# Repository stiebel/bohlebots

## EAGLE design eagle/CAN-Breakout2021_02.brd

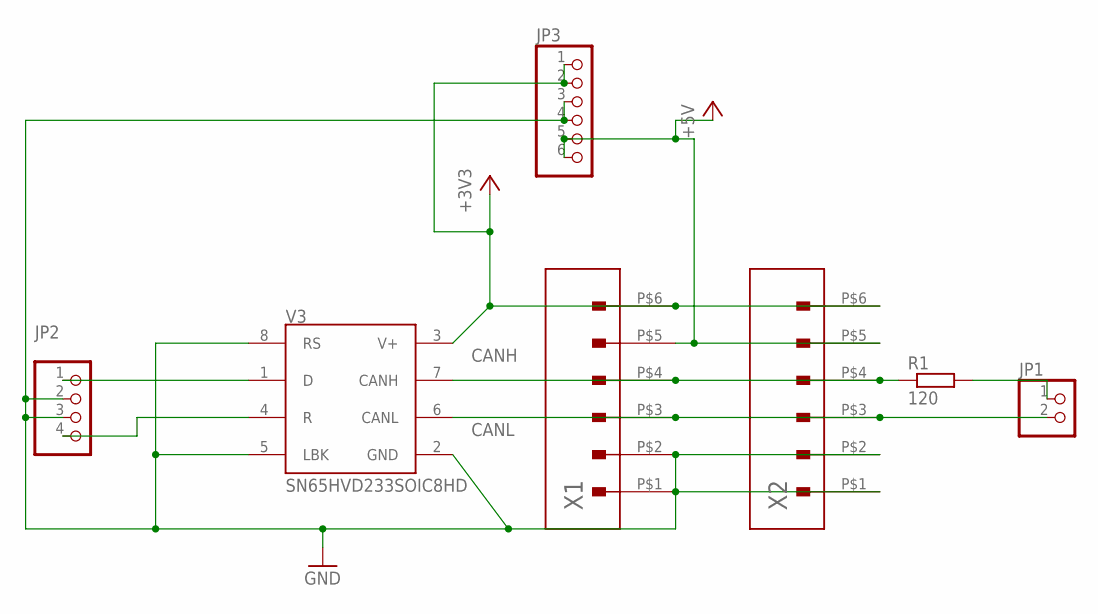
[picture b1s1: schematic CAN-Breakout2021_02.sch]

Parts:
JP1: PINHD-1X2/90; 1X02/90
JP2: PINHD-1X4; 1X04
JP3: PINHD-1X6; 1X06
R1: 120; R0603
V3: SN65HVD233SOIC8HD; SO08
X1, X2: MOLEX104078-0610

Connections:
+3V3: JP3.1, JP3.2, V3.3 (V+), X1.P$6 (6), X2.P$6 (6)
+5V: JP3.5, JP3.6, X1.P$5 (5), X2.P$5 (5)
CANH: R1.1, V3.7 (CANH), X1.P$4 (4), X2.P$4 (4)
CANL: JP1.2, V3.6 (CANL), X1.P$3 (3), X2.P$3 (3)
GND: JP2.2, JP2.3, JP3.3, JP3.4, V3.2 (GND), V3.5 (LBK), V3.8 (RS), X1.P$1 (1), X1.P$2 (2), X2.P$1 (1), X2.P$2 (2)
unnamed: JP1.1, R1.2
unnamed: JP2.1, V3.1 (D)
unnamed: JP2.4, V3.4 (R)

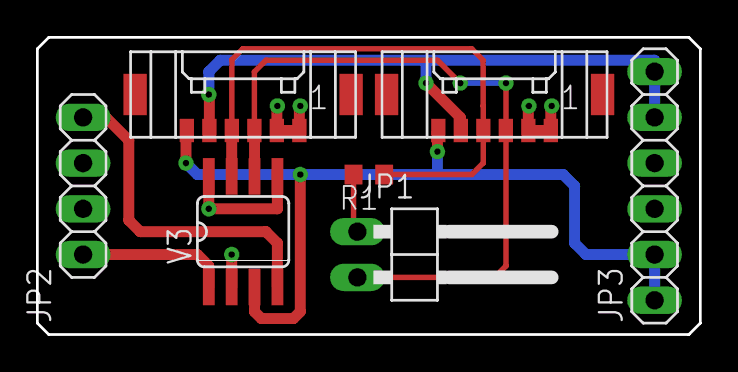
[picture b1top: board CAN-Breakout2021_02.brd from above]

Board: 2 copper layers, 36.8 x 16.5 mm, 7 parts (0 on the bottom side), 8 nets.

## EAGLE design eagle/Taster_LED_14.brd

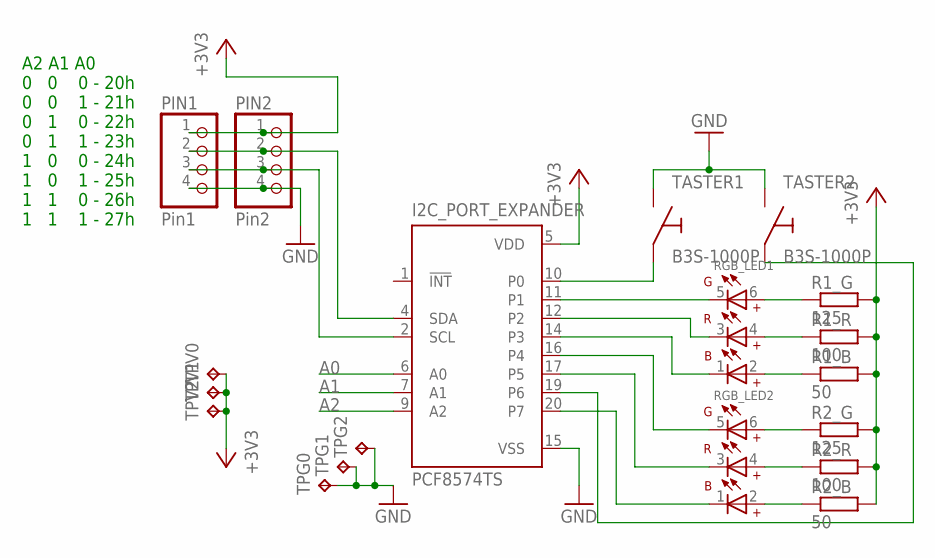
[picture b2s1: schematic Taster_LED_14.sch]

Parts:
I2C_PORT_EXPANDER: PCF8574TS; SSOP20
PIN1: Pin1; 1X04
PIN2: Pin2; 1X04
R1_B, R2_B: 50; R0603
R1_G, R2_G: 125; R0603
R1_R, R2_R: 100; R0603
RGB_LED1, RGB_LED2: WL-SFTW_3528_PLCC6_150352M173300; WL-SFTW_3528_PLCC6
TASTER1, TASTER2: B3S-1000P; B3S-100P
TPG0, TPG1, TPG2: TPTP06SQ; TP06SQ
TPV0, TPV1, TPV2: TPTP06SQ; TP06SQ

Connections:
+3V3: I2C_PORT_EXPANDER.5 (VDD), PIN1.1, PIN2.1, R1_B.2, R1_G.2, R1_R.2, R2_B.2, R2_G.2, R2_R.2, TPV0.TP, TPV1.TP, TPV2.TP
A0: I2C_PORT_EXPANDER.6 (A0)
A1: I2C_PORT_EXPANDER.7 (A1)
A2: I2C_PORT_EXPANDER.9 (A2)
CLK: I2C_PORT_EXPANDER.2 (SCL), PIN1.3, PIN2.3
DATA: I2C_PORT_EXPANDER.4 (SDA), PIN1.2, PIN2.2
GND: I2C_PORT_EXPANDER.15 (VSS), PIN1.4, PIN2.4, TASTER1.3 (2), TASTER2.3 (2), TPG0.TP, TPG1.TP, TPG2.TP
unnamed: I2C_PORT_EXPANDER.11 (P1), RGB_LED1.5
unnamed: R2_B.1, RGB_LED2.2
unnamed: R2_R.1, RGB_LED2.4
unnamed: R2_G.1, RGB_LED2.6
unnamed: R1_G.1, RGB_LED1.6
unnamed: R1_R.1, RGB_LED1.4
unnamed: R1_B.1, RGB_LED1.2
unnamed: I2C_PORT_EXPANDER.19 (P6), TASTER2.1
P0: I2C_PORT_EXPANDER.10 (P0), TASTER1.1
P3: I2C_PORT_EXPANDER.12 (P2), RGB_LED1.3
P4: I2C_PORT_EXPANDER.14 (P3), RGB_LED1.1
P5: I2C_PORT_EXPANDER.16 (P4), RGB_LED2.5
P6: I2C_PORT_EXPANDER.17 (P5), RGB_LED2.3
P7: I2C_PORT_EXPANDER.20 (P7), RGB_LED2.1

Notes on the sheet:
A2 A1 A0 0 0 0 - 20h 0 0 1 - 21h 0 1 0 - 22h 0 1 1 - 23h 1 0 0 - 24h 1 0 1 - 25h 1 1 0 - 26h 1 1 1 - 27h

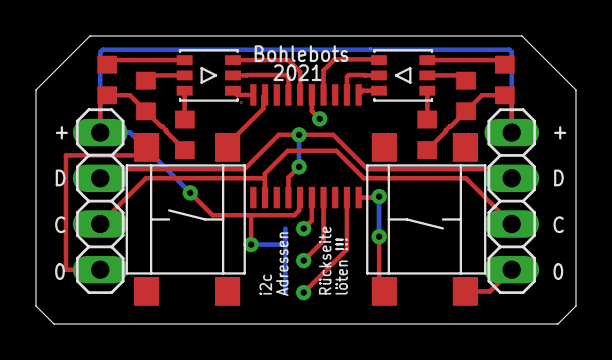
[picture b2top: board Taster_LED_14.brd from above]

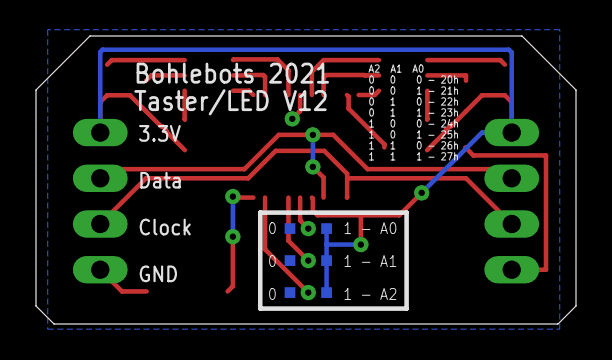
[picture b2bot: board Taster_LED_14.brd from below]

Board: 2 copper layers, 30.0 x 16.0 mm, 19 parts (6 on the bottom side), 18 nets.

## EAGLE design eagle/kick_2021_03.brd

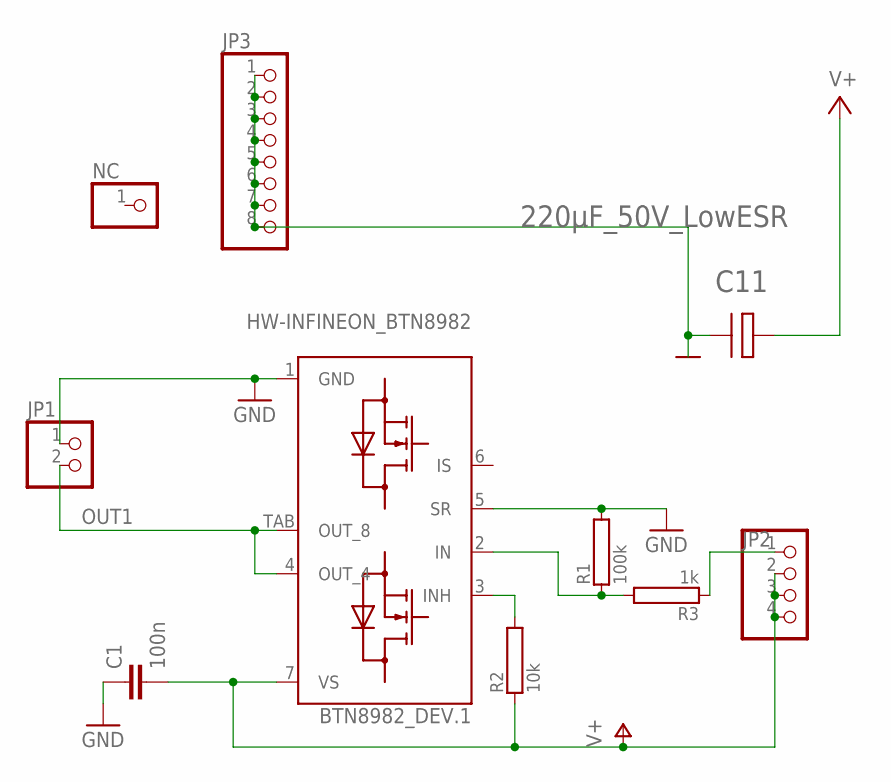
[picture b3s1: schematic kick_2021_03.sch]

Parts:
BTN8982_DEV.1: HW-INFINEON_BTN8982; HW-INFINEON_TO263-7-1
C1: 100n; 0603-CAP
C11: 220µF_50V_LowESR; 470µF/SMD/16V
JP1: PINHD-1X2/90; 1X02/90
JP2: PINHD-1X4; 1X04
JP3: PINHD-1X8; 1X08
NC: PINHD-1X1; 1X01
R1: 100k; 0603
R2: 10k; 0603
R3: 1k; 0603

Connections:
GND: BTN8982_DEV.1.1 (GND), BTN8982_DEV.1.5 (SR), C1.1, C11.-, JP1.1, JP3.1, JP3.2, JP3.3, JP3.4, JP3.5, JP3.6, JP3.7, JP3.8, R1.2
unnamed: BTN8982_DEV.1.3 (INH), R2.2
unnamed: BTN8982_DEV.1.2 (IN), R1.1, R3.2
unnamed: JP2.1, R3.1
OUT1: BTN8982_DEV.1.4 (OUT_4), BTN8982_DEV.1.TAB (OUT_8), JP1.2
V+: BTN8982_DEV.1.7 (VS), C1.2, C11.+, JP2.2, JP2.3, JP2.4, R2.1

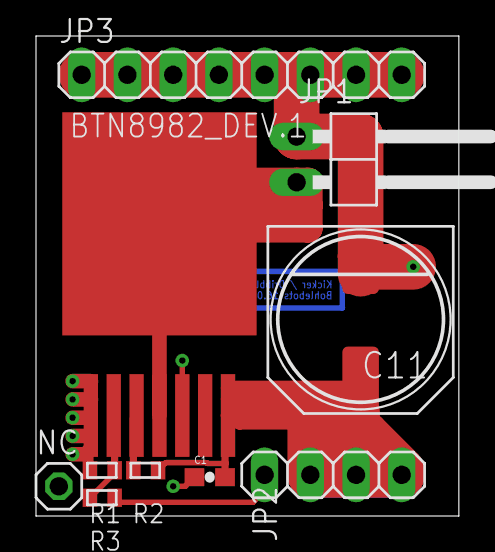
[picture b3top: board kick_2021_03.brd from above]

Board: 2 copper layers, 23.5 x 26.7 mm, 10 parts (0 on the bottom side), 6 nets.

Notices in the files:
parts and their libraries:
Eagle_COLOR_LED: Copyright: Würth Elektronik
